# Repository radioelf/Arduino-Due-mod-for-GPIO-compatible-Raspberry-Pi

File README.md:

# Arduino Due mod for GPIO compatible Raspberry Pi
Creative Commons License Disclaimer

UNLESS OTHERWISE MUTUALLY AGREED TO BY THE PARTIES IN WRITING, LICENSOR OFFERS THE WORK AS-IS AND MAKES NO REPRESENTATIONS 
OR WARRANTIES OF ANY KIND CONCERNING THE WORK, EXPRESS, IMPLIED, STATUTORY OR OTHERWISE, INCLUDING, WITHOUT LIMITATION,
WARRANTIES OF TITLE, MERCHANTIBILITY, FITNESS FOR A PARTICULAR PURPOSE, NONINFRINGEMENT, OR THE ABSENCE OF LATENT OR 
OTHER DEFECTS, ACCURACY, OR THE PRESENCE OF ABSENCE OF ERRORS, WHETHER OR NOT DISCOVERABLE. SOME JURISDICTIONS DO NOT 
ALLOW THE EXCLUSION OF IMPLIED WARRANTIES, SO SUCH EXCLUSION MAY NOT APPLY TO YOU. EXCEPT TO THE EXTENT REQUIRED BY 
APPLICABLE LAW, IN NO EVENT WILL LICENSOR BE LIABLE TO YOU ON ANY LEGAL THEORY FOR ANY SPECIAL, INCIDENTAL, CONSEQUENTIAL, 
PUNITIVE OR EXEMPLARY DAMAGES ARISING OUT OF THIS LICENSE OR THE USE OF THE WORK, EVEN IF LICENSOR HAS BEEN ADVISED OF 
THE POSSIBILITY OF SUCH DAMAGES.

http://creativecommons.org/licenses/by-sa/3.0/

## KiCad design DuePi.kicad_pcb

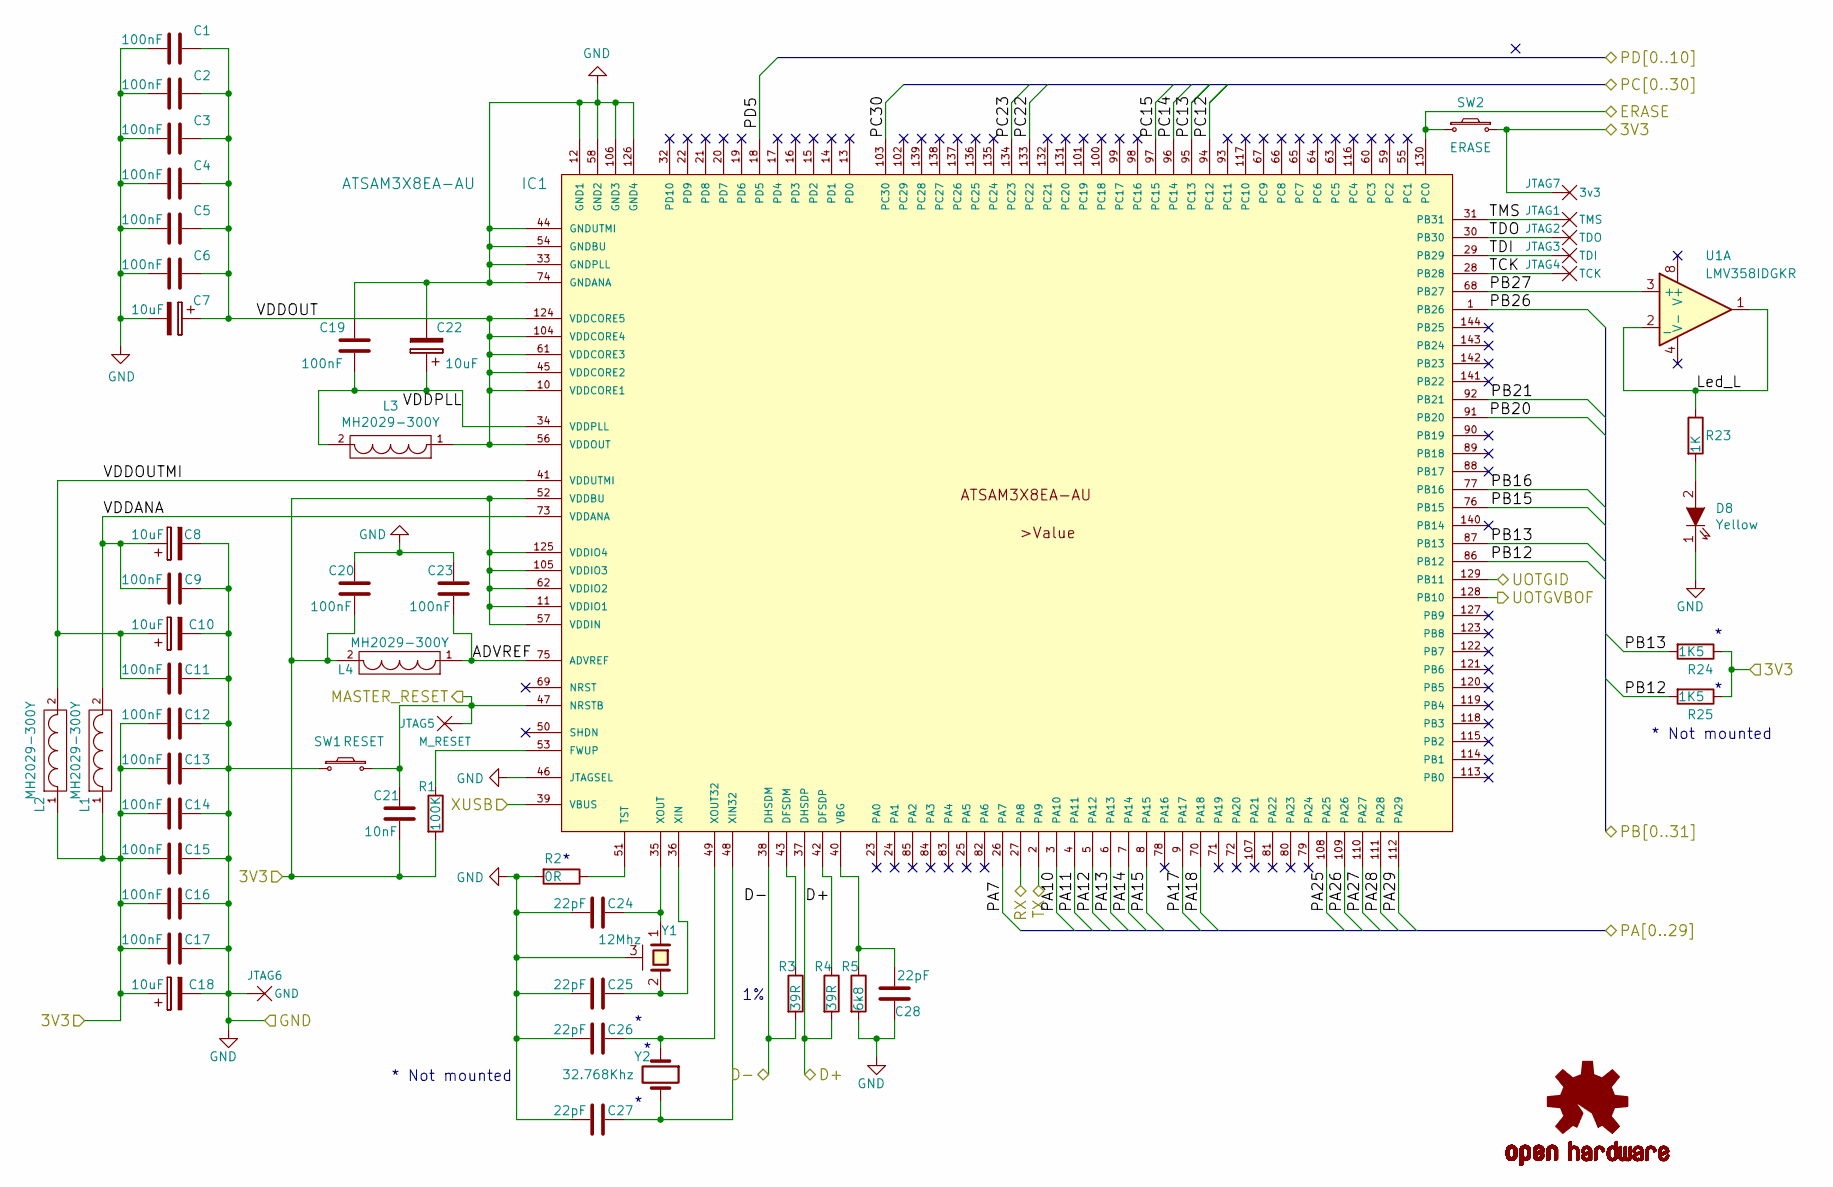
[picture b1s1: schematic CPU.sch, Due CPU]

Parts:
C1, C2, C3, C4, C5, C6, C9, C11, C12, C13, C14, C15, C16, C17, C19, C20, C23: 100nF; C_0402
C7, C8, C10, C18, C22: 10uF; C_1210_HandSoldering
C21: 10nF; C_0402
C24, C25, C26, C27, C28: 22pF; C_0402
D8: Yellow; LED_0603
IC1: ATSAM3X8EA-AU; LQFP-144_20x20mm_Pitch0.5mm
JTAG1: TMS; Measurement_Point_Round-TH_Small
JTAG2: TDO; Measurement_Point_Round-TH_Small
JTAG3: TDI; Measurement_Point_Round-TH_Small
JTAG4: TCK; Measurement_Point_Round-TH_Small
JTAG5: M_RESET; Measurement_Point_Round-TH_Small
JTAG6: GND; Measurement_Point_Round-TH_Small
JTAG7: 3v3; Measurement_Point_Round-TH_Small
L1, L2, L3, L4: MH2029-300Y; R_0805
M2: OSHW-LOGOL; OSHW-LOGO-L
R1: 100K; R_0402
R2: 0R; R_0402
R3, R4: 39R; R_0402
R5: 6k8; R_0603
R23: 1K; R_0402
R24, R25: 1K5; R_0402
SW1: RESET; SW_SPST_B3S-1000
SW2: ERASE; SW_SPST_EVQPE1
U1: LMV358IDGKR; MSOP8
Y1: 12Mhz; Crystal_SMD_2520_4Pads
Y2: 32.768Khz; Crystal_SMD_5032_2Pads

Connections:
/CPU_Due/3V3: C12.1, C13.1, C14.1, C15.1, C16.1, C17.1, C18.1, C20.1, C21.1, IC1.11 (VDDIO1), IC1.52 (VDDBU), IC1.57 (VDDIN), IC1.62 (VDDIO2), IC1.105 (VDDIO3), IC1.125 (VDDIO4), JTAG7.1, L1.1, L2.1, L4.2, R1.2, R24.1, R25.1, SW2.2; also elsewhere on the board
/CPU_Due/ADVREF: C23.1, IC1.75 (ADVREF), L4.1
/CPU_Due/D+: IC1.37 (DHSDP), R4.2; also elsewhere on the board
/CPU_Due/D-: IC1.38 (DHSDM), R3.2; also elsewhere on the board
/CPU_Due/ERASE: IC1.130 (PC0), SW2.1; also elsewhere on the board
/CPU_Due/Led_L: R23.1, U1.1, U1.2 (_)
/CPU_Due/MASTER_RESET: C21.2, IC1.47 (NRSTB), JTAG5.1, SW1.2; also elsewhere on the board
/CPU_Due/PB27: IC1.68 (PB27), U1.3 (+)
/CPU_Due/RX: IC1.27 (PA8); also elsewhere on the board
/CPU_Due/TCK: IC1.28 (PB28), JTAG4.1
/CPU_Due/TDI: IC1.29 (PB29), JTAG3.1
/CPU_Due/TDO: IC1.30 (PB30), JTAG2.1
/CPU_Due/TMS: IC1.31 (PB31), JTAG1.1
/CPU_Due/TX: IC1.2 (PA9); also elsewhere on the board
/CPU_Due/UOTGID: IC1.129 (PB11); also elsewhere on the board
/CPU_Due/UOTGVBOF: IC1.128 (PB10); also elsewhere on the board
/CPU_Due/VDDANA: C8.1, C9.1, IC1.73 (VDDANA), L1.2
/CPU_Due/VDDOUT: C1.2, C2.2, C3.2, C4.2, C5.2, C6.2, C7.1, IC1.10 (VDDCORE1), IC1.45 (VDDCORE2), IC1.56 (VDDOUT), IC1.61 (VDDCORE3), IC1.104 (VDDCORE4), IC1.124 (VDDCORE5), L3.1
/CPU_Due/VDDOUTMI: C10.1, C11.1, IC1.41 (VDDUTMI), L2.2
/CPU_Due/VDDPLL: C19.1, C22.1, IC1.34 (VDDPLL), L3.2
/CPU_Due/XUSB: IC1.39 (VBUS); also elsewhere on the board
/DronPi_GPIO/AUX1: IC1.95 (PC13); also elsewhere on the board
/DronPi_GPIO/AUX2: IC1.94 (PC12); also elsewhere on the board
/DronPi_GPIO/AUX3: IC1.77 (PB16); also elsewhere on the board
/DronPi_GPIO/AUX4: IC1.91 (PB20); also elsewhere on the board
/DronPi_GPIO/AUX5: IC1.96 (PC14); also elsewhere on the board
/DronPi_GPIO/BUZZER: IC1.76 (PB15); also elsewhere on the board
/DronPi_GPIO/CS_BARO: IC1.111 (PA28); also elsewhere on the board
/DronPi_GPIO/CS_CAN: IC1.92 (PB21); also elsewhere on the board
/DronPi_GPIO/CS_MPU: IC1.112 (PA29); also elsewhere on the board
/DronPi_GPIO/CTS: IC1.8 (PA15); also elsewhere on the board
/DronPi_GPIO/ENABLE: IC1.26 (PA7); also elsewhere on the board
/DronPi_GPIO/INT_CAN: IC1.3 (PA10); also elsewhere on the board
/DronPi_GPIO/INT_MPU: IC1.1 (PB26); also elsewhere on the board
/DronPi_GPIO/LED_Green: IC1.134 (PC23); also elsewhere on the board
/DronPi_GPIO/LED_Red: IC1.133 (PC22); also elsewhere on the board
/DronPi_GPIO/LED_Yellow: IC1.103 (PC30); also elsewhere on the board
/DronPi_GPIO/MISO: IC1.108 (PA25); also elsewhere on the board
/DronPi_GPIO/MOSI: IC1.109 (PA26); also elsewhere on the board
/DronPi_GPIO/POWER_OFF: IC1.97 (PC15); also elsewhere on the board
/DronPi_GPIO/PPM: IC1.18 (PD5); also elsewhere on the board
/DronPi_GPIO/PWM_EN: IC1.4 (PA11); also elsewhere on the board
/DronPi_GPIO/RTS: IC1.7 (PA14); also elsewhere on the board
/DronPi_GPIO/RXD: IC1.5 (PA12); also elsewhere on the board
/DronPi_GPIO/SCL: IC1.87 (PB13), R24.2; also elsewhere on the board
/DronPi_GPIO/SCL1: IC1.70 (PA18); also elsewhere on the board
/DronPi_GPIO/SDA: IC1.86 (PB12), R25.2; also elsewhere on the board
/DronPi_GPIO/SDA1: IC1.9 (PA17); also elsewhere on the board
/DronPi_GPIO/SPCK: IC1.110 (PA27); also elsewhere on the board
/DronPi_GPIO/TXD: IC1.6 (PA13); also elsewhere on the board
/Power_Due/+5V: U1.8 (V+); also elsewhere on the board
GND: C1.1, C2.1, C3.1, C4.1, C5.1, C6.1, C7.2, C8.2, C9.2, C10.2, C11.2, C12.2, C13.2, C14.2, C15.2, C16.2, C17.2, C18.2, C19.2, C20.2, C22.2, C23.2, C24.1, C25.1, C26.1, C27.1, C28.2, D8.1 (K), IC1.12 (GND1), IC1.33 (GNDPLL), IC1.44 (GNDUTMI), IC1.46 (JTAGSEL), IC1.54 (GNDBU), IC1.58 (GND2), IC1.74 (GNDANA), IC1.106 (GND3), IC1.126 (GND4), JTAG6.1, R2.2, R5.2, SW1.1, U1.4 (V-), Y1.3 (case); also elsewhere on the board
unnamed: C24.2, IC1.35 (XOUT), Y1.1
unnamed: C25.2, IC1.36 (XIN), Y1.2
unnamed: C26.2, IC1.49 (XOUT32), Y2.1
unnamed: C27.2, IC1.48 (XIN32), Y2.2
unnamed: C28.1, IC1.40 (VBG), R5.1
unnamed: D8.2 (A), R23.2
unnamed: IC1.42 (DFSDP), R4.1
unnamed: IC1.43 (DFSDM), R3.1
unnamed: IC1.51 (TST), R2.1
unnamed: IC1.53 (FWUP), R1.1

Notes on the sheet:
* Not mounted

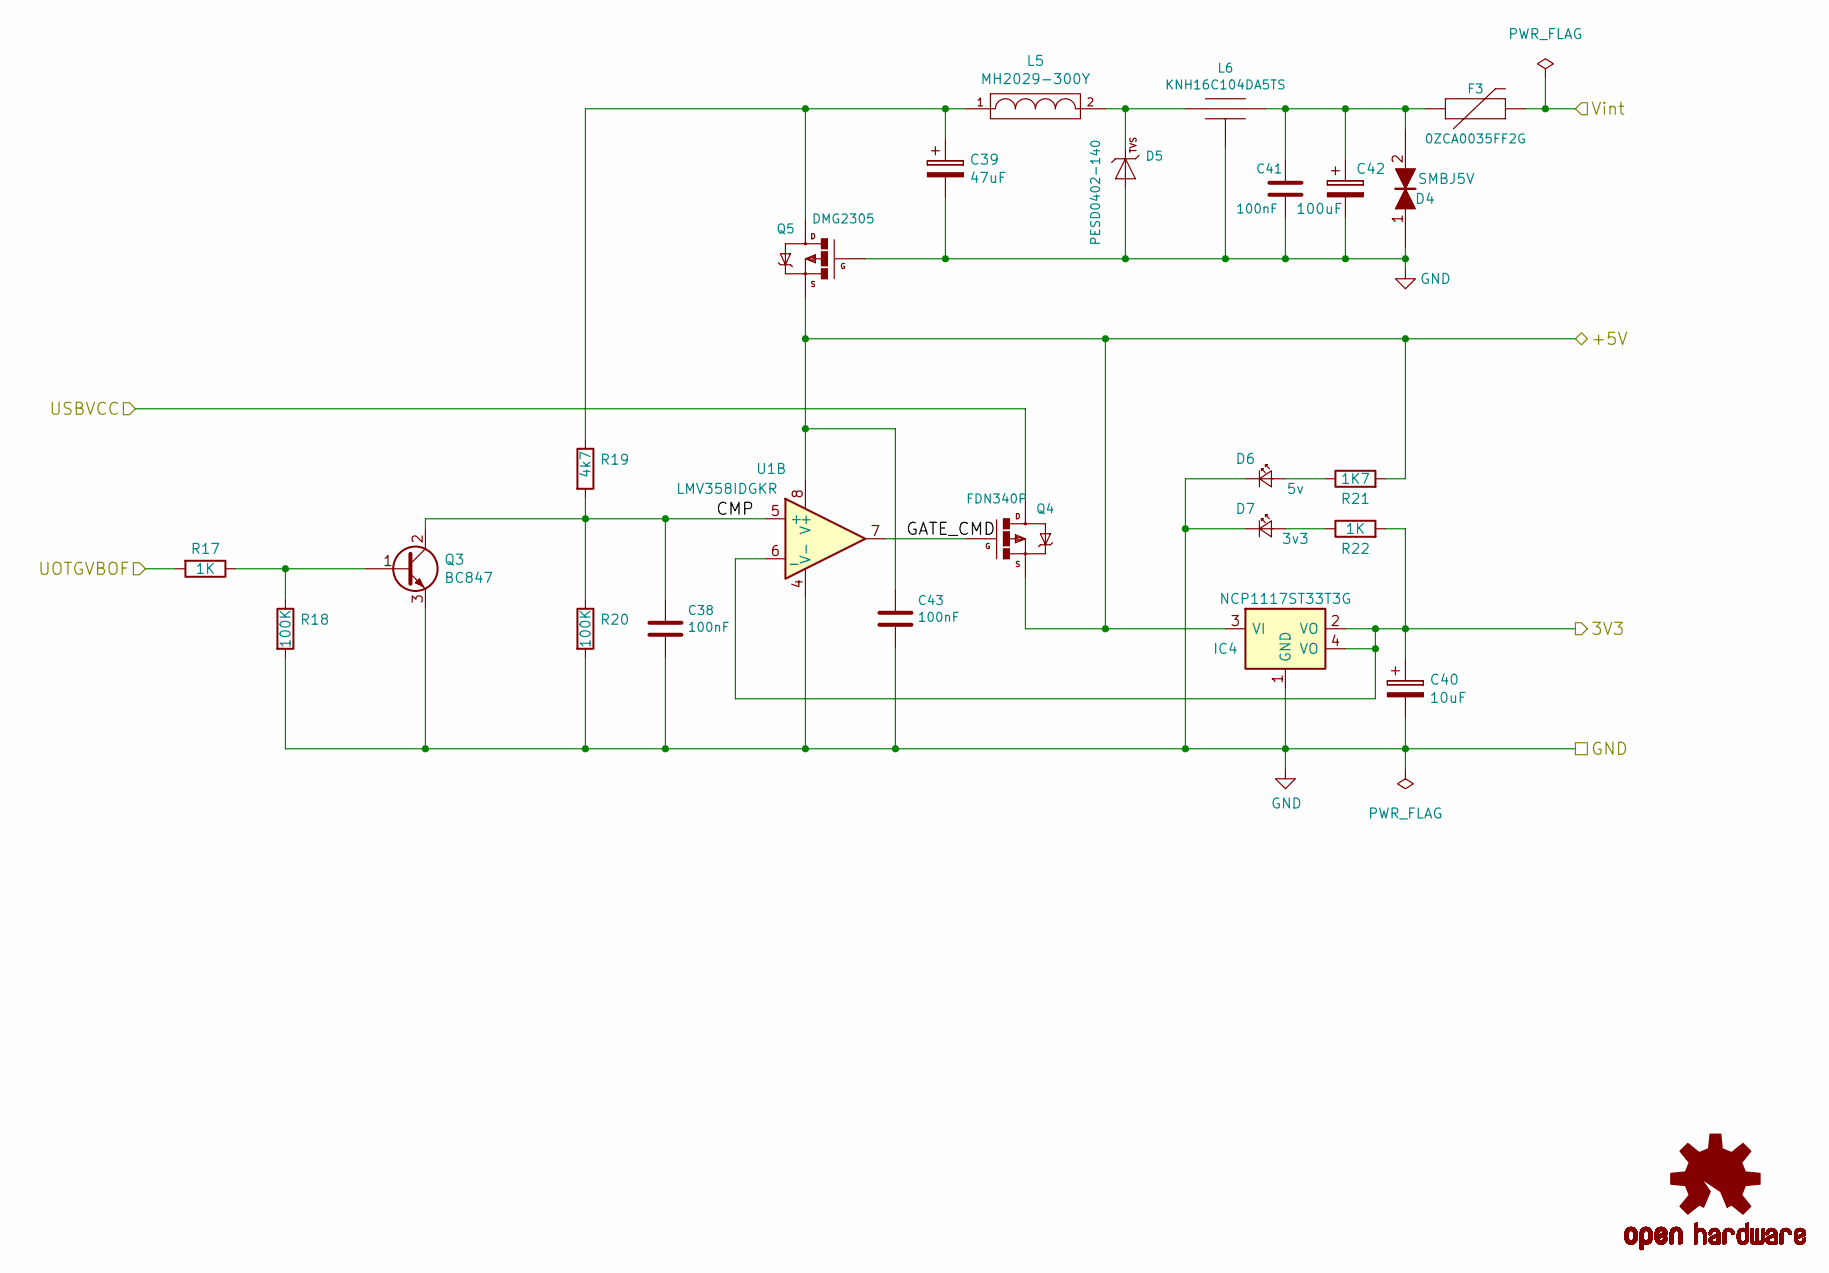
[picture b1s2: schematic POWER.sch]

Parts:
C38, C41, C43: 100nF; C_0402
C39: 47uF; C_1210_HandSoldering
C40: 10uF; C_1210_HandSoldering
C42: 100uF; TantalC_SizeD_EIA-7343_Reflow
D4: SMBJ5V; DO-214AA
D5: PESD0402-140; C_0402
D6: 5v; LED_0603
D7: 3v3; LED_0603
F3: 0ZCA0035FF2G; Fuse_SMD1206_Wave
IC4: NCP1117ST33T3G; SOT-223
L5: MH2029-300Y; R_0805
L6: KNH16C104DA5TS; KYOCERA-KNH16-DA
M3: OSHW-LOGOL; OSHW-LOGO-L
Q3: BC847; SOT-23
Q4: FDN340P; SOT-23
Q5: DMG2305; SOT-23
R17, R22: 1K; R_0402
R18, R20: 100K; R_0402
R19: 4k7; R_0402
R21: 1K7; R_0402
U1: LMV358IDGKR; MSOP8

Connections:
/CPU_Due/3V3: C40.1, IC4.2 (VO), IC4.4 (VO), R22.2, U1.6 (_); also elsewhere on the board
/CPU_Due/UOTGVBOF: R17.2; also elsewhere on the board
/DronPi_GPIO/Vint: F3.2; also elsewhere on the board
/Power_Due/+5V: C43.1, IC4.3 (VI), Q4.2 (S), Q5.2 (S), R21.2, U1.8 (V+); also elsewhere on the board
/Power_Due/CMP: C38.1, Q3.2 (C), R19.2, R20.1, U1.5 (+)
/Power_Due/GATE_CMD: Q4.1 (G), U1.7
/Power_Due/USBVCC: Q4.3 (D); also elsewhere on the board
GND: C38.2, C39.2, C40.2, C41.2, C42.2, C43.2, D4.1, D5.2 (A), D6.1 (K), D7.1 (K), IC4.1 (GND), L6.P$3, L6.P$4, L6.P$5, Q3.3 (E), Q5.1 (G), R18.2, R20.2, U1.4 (V-); also elsewhere on the board
unnamed: C39.1, L5.1, Q5.3 (D), R19.1
unnamed: C41.1, C42.1, D4.2, F3.1, L6.P$2
unnamed: D5.1 (C), L5.2, L6.P$1
unnamed: D6.2 (A), R21.1
unnamed: D7.2 (A), R22.1
unnamed: Q3.1 (B), R17.1, R18.1

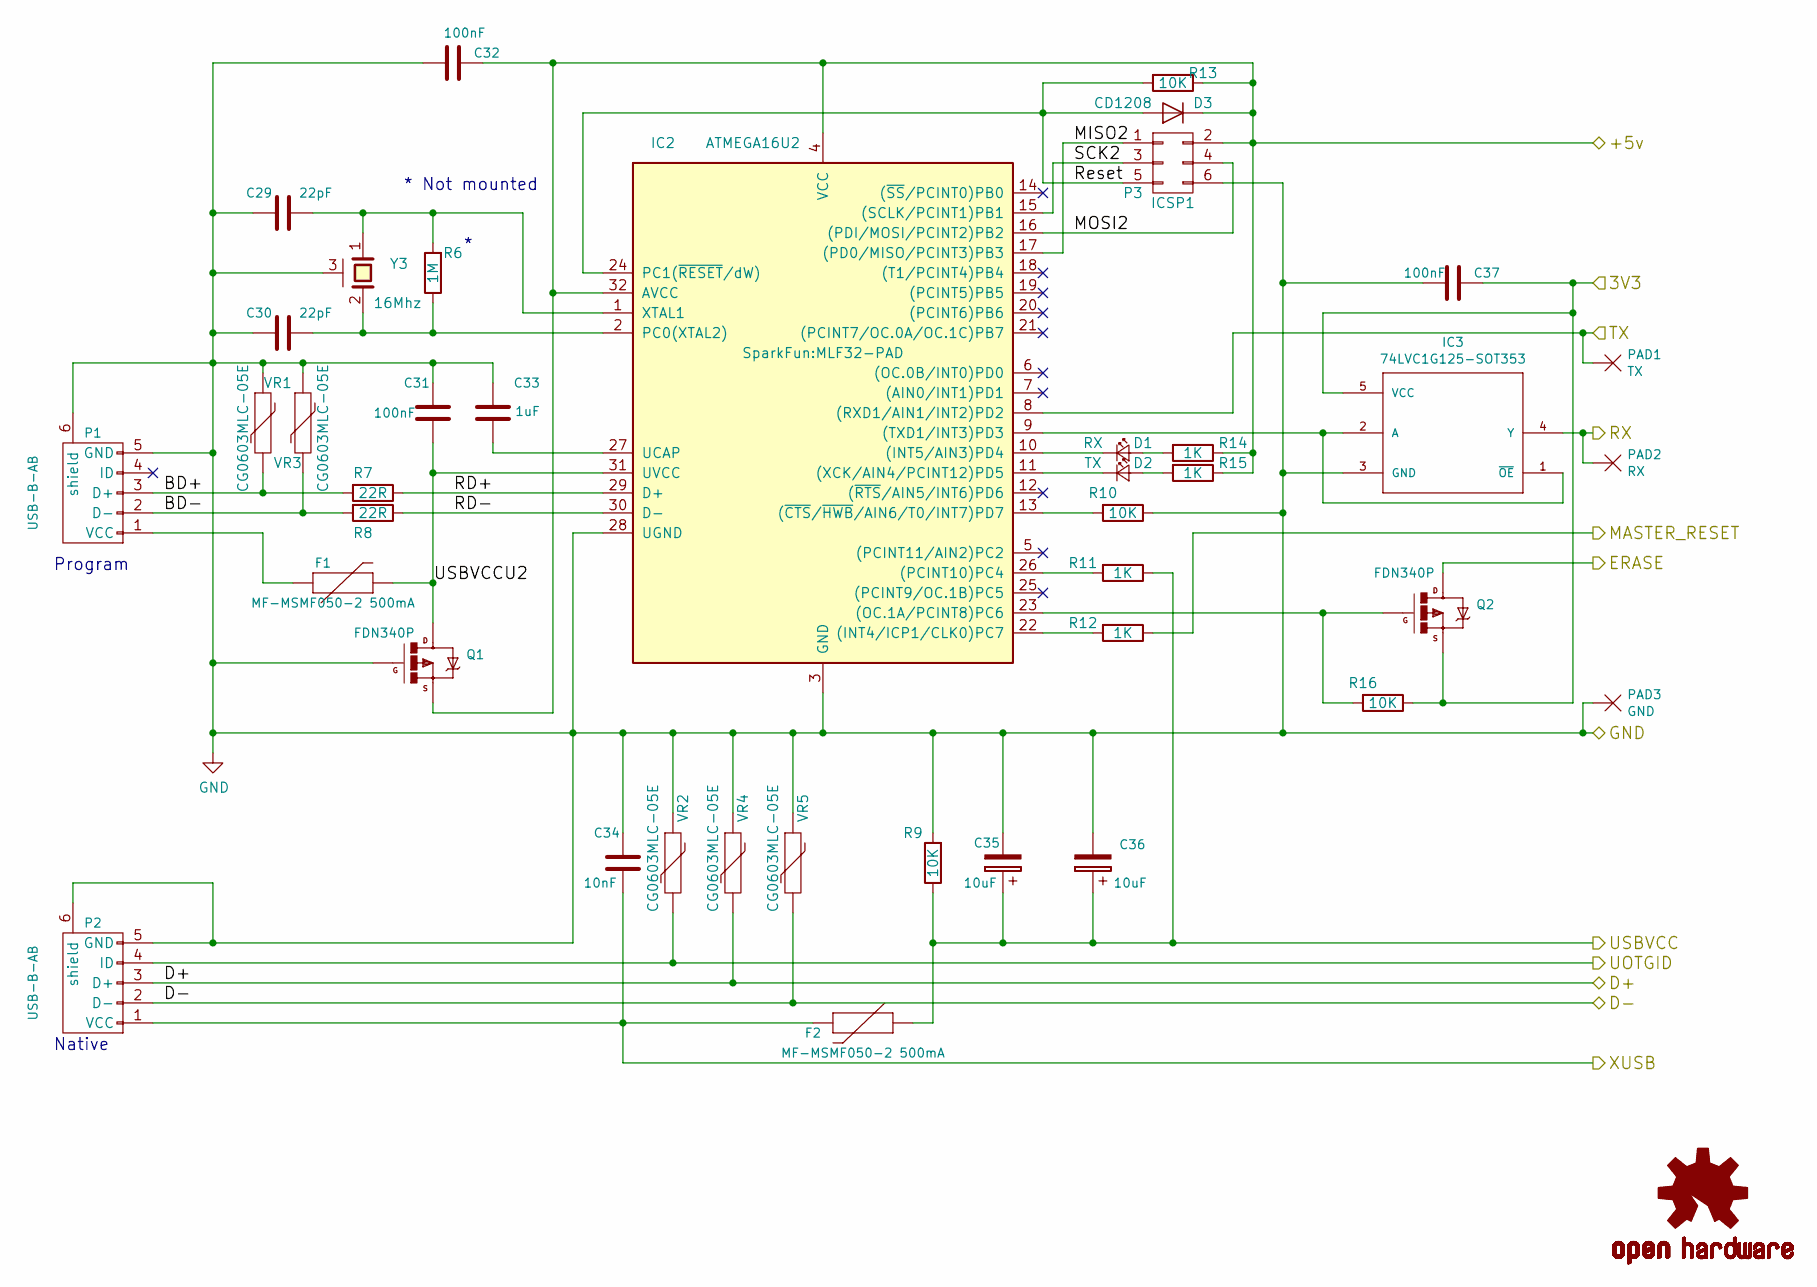
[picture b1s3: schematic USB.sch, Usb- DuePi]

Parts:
C29, C30: 22pF; C_0402
C31, C32, C37: 100nF; C_0402
C33: 1uF; C_0402
C34: 10nF; C_0402
C35, C36: 10uF; C_1210_HandSoldering
D1: RX; LED_0603
D2: TX; LED_0603
D3: CD1208; D_1206
F1, F2: MF-MSMF050-2 500mA; Neosid_Inductor_SM-NE45_SMD1812
IC2: ATMEGA16U2; MLF32-PAD
IC3: 74LVC1G125-SOT353; SC70-5
M5: OSHW-LOGOL; OSHW-LOGO-L
P1, P2: USB-B-AB; USB_Micro-B
P3: ICSP1; Pin_Header_Straight_2x03
PAD1: TX; Measurement_Point_Square-TH_Small
PAD2: RX; Measurement_Point_Square-TH_Small
PAD3: GND; Measurement_Point_Square-TH_Small
Q1, Q2: FDN340P; SOT-23
R6: 1M; R_0402
R7, R8: 22R; R_0402
R9, R10, R13, R16: 10K; R_0402
R11, R12, R14, R15: 1K; R_0402
VR1, VR2, VR3, VR4, VR5: CG0603MLC-05E; Neosid_Inductor_SM0603CG
Y3: 16Mhz; Crystal_SMD_2520_4Pads

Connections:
/CPU_Due/3V3: C37.1, IC3.5 (VCC), Q2.2 (S), R16.1; also elsewhere on the board
/CPU_Due/D+: P2.3 (D+), VR4.2; also elsewhere on the board
/CPU_Due/D-: P2.2 (D-), VR5.2; also elsewhere on the board
/CPU_Due/ERASE: Q2.3 (D); also elsewhere on the board
/CPU_Due/MASTER_RESET: R12.1; also elsewhere on the board
/CPU_Due/RX: IC3.4 (Y), PAD2.1; also elsewhere on the board
/CPU_Due/TX: IC2.8 ((RXD1/AIN1/INT2)PD2), PAD1.1; also elsewhere on the board
/CPU_Due/UOTGID: P2.4 (ID), VR2.2; also elsewhere on the board
/CPU_Due/XUSB: C34.2, F2.2, P2.1 (VCC); also elsewhere on the board
/Power_Due/+5V: C32.1, D3.1 (K), IC2.4 (VCC), IC2.32 (AVCC), P3.2, Q1.2 (S), R13.1, R14.1, R15.1; also elsewhere on the board
/Power_Due/USBVCC: C35.1, C36.1, F2.1, R9.1, R11.1; also elsewhere on the board
/USB_Due/BD+: P1.3 (D+), R7.2, VR1.2
/USB_Due/BD-: P1.2 (D-), R8.2, VR3.2
/USB_Due/MISO2: IC2.17 ((PD0/MISO/PCINT3)PB3), P3.1
/USB_Due/MOSI2: IC2.16 ((PDI/MOSI/PCINT2)PB2), P3.4
/USB_Due/RD+: IC2.29 (D+), R7.1
/USB_Due/RD-: IC2.30 (D-), R8.1
/USB_Due/Reset: D3.2 (A), IC2.24 (PC1(~RESET~/dW)), P3.5, R13.2
/USB_Due/SCK2: IC2.15 ((SCLK/PCINT1)PB1), P3.3
/USB_Due/USBVCCU2: C31.2, F1.2, IC2.31 (UVCC), Q1.3 (D)
GND: C29.1, C30.1, C31.1, C32.2, C33.1, C34.1, C35.2, C36.2, C37.2, IC2.3 (GND), IC2.28 (UGND), IC3.3 (GND), P1.5 (GND), P1.6 (shield), P2.5 (GND), P2.6 (shield), P3.6, PAD3.1, Q1.1 (G), R9.2, R10.1, VR1.1, VR2.1, VR3.1, VR4.1, VR5.1, Y3.3 (case); also elsewhere on the board
unnamed: C29.2, IC2.1 (XTAL1), R6.2, Y3.1
unnamed: C30.2, IC2.2 (PC0(XTAL2)), R6.1, Y3.2
unnamed: C33.2, IC2.27 (UCAP)
unnamed: D1.1 (K), IC2.10 ((INT5/AIN3)PD4)
unnamed: D1.2 (A), R14.2
unnamed: D2.1 (K), IC2.11 ((XCK/AIN4/PCINT12)PD5)
unnamed: D2.2 (A), R15.2
unnamed: F1.1, P1.1 (VCC)
unnamed: IC2.9 ((TXD1/INT3)PD3), IC3.1 (~OE), IC3.2 (A)
unnamed: IC2.13 ((~CTS~/~HWB~/AIN6/T0/INT7)PD7), R10.2
unnamed: IC2.22 ((INT4/ICP1/CLK0)PC7), R12.2
unnamed: IC2.23 ((OC.1A/PCINT8)PC6), Q2.1 (G), R16.2
unnamed: IC2.26 ((PCINT10)PC4), R11.2

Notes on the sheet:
Program
Native
* Not mounted

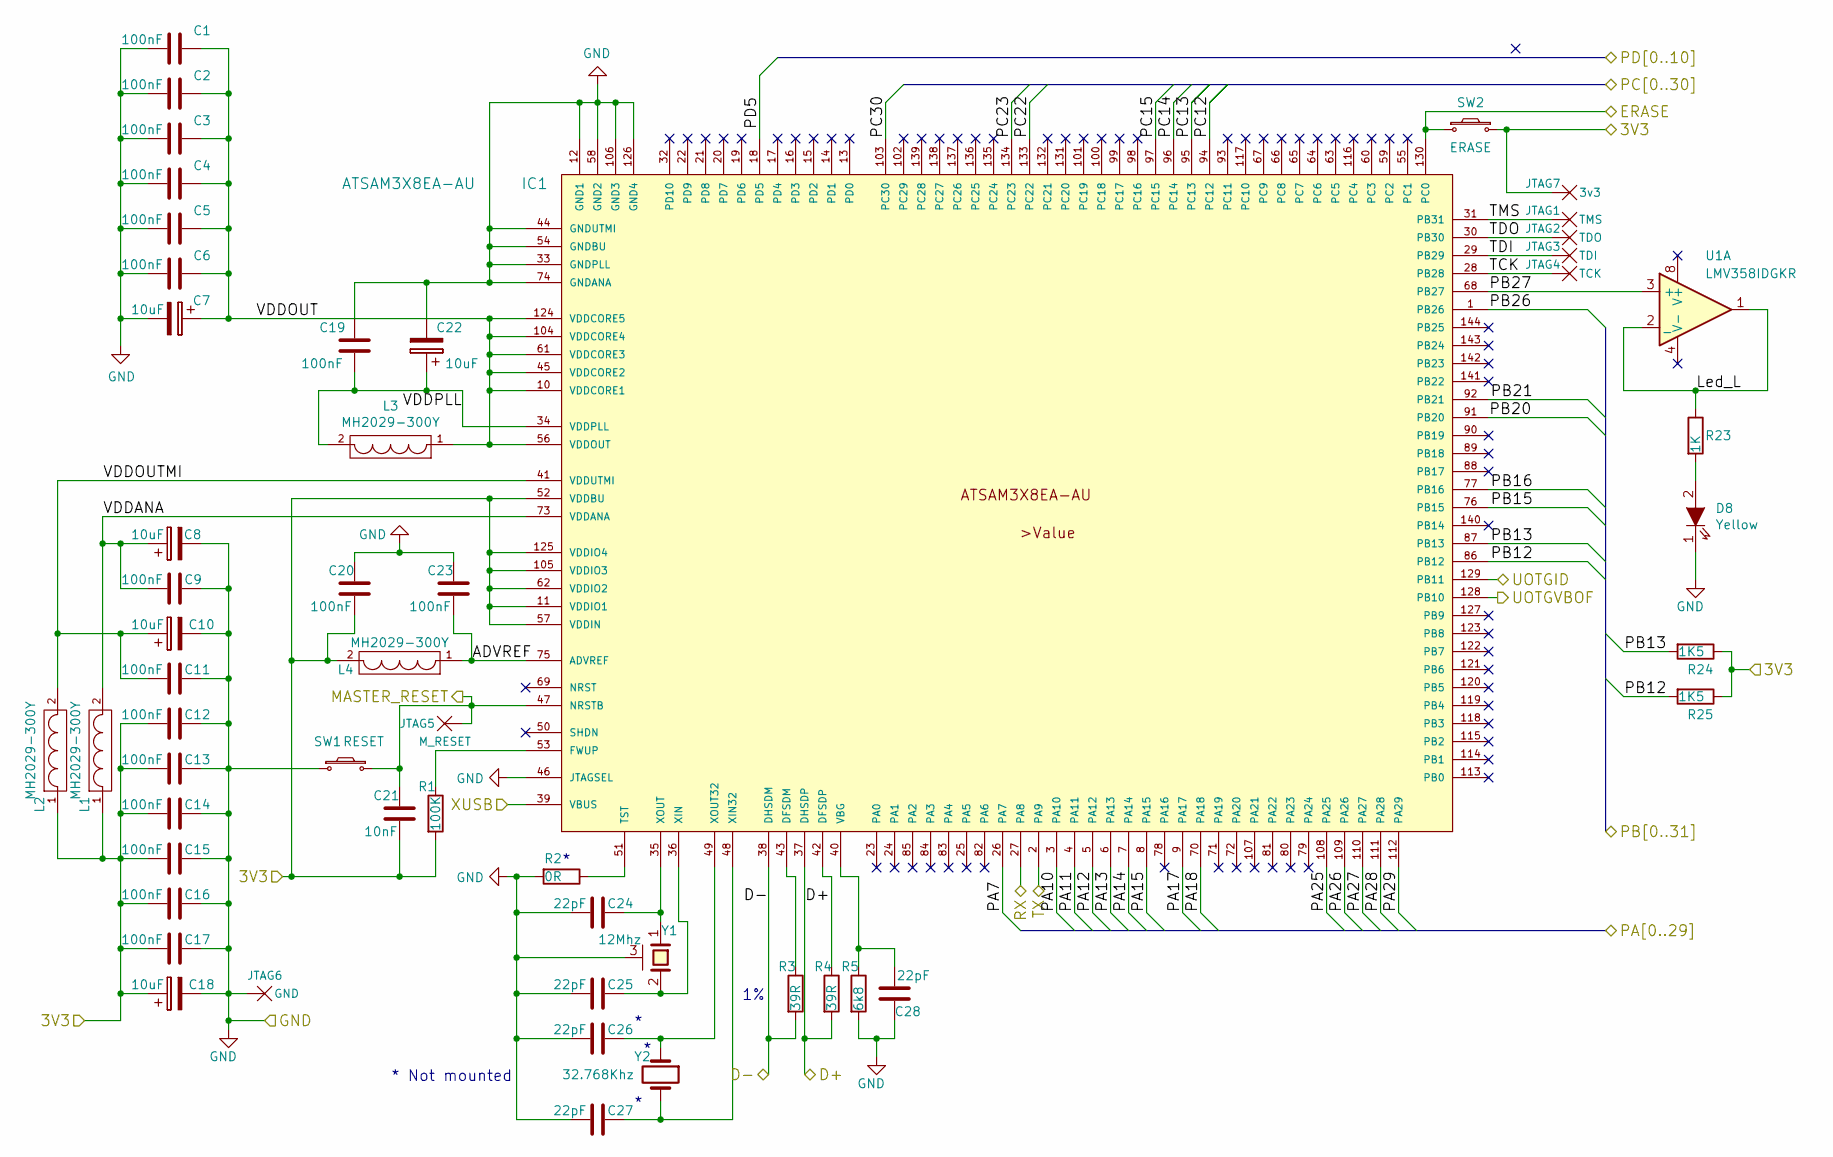
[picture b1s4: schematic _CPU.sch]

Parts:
C1, C2, C3, C4, C5, C6, C9, C11, C12, C13, C14, C15, C16, C17, C19, C20, C23: 100nF; C_0402
C7, C8, C10, C18, C22: 10uF; C_1210_HandSoldering
C21: 10nF; C_0402
C24, C25, C26, C27, C28: 22pF; C_0402
D8: Yellow; LED_0603
IC1: ATSAM3X8EA-AU; LQFP-144_20x20mm_Pitch0.5mm
JTAG1: TMS; Measurement_Point_Round-TH_Small
JTAG2: TDO; Measurement_Point_Round-TH_Small
JTAG3: TDI; Measurement_Point_Round-TH_Small
JTAG4: TCK; Measurement_Point_Round-TH_Small
JTAG5: M_RESET; Measurement_Point_Round-TH_Small
JTAG6: GND; Measurement_Point_Round-TH_Small
JTAG7: 3v3; Measurement_Point_Round-TH_Small
L1, L2, L3, L4: MH2029-300Y; R_0805
R1: 100K; R_0402
R2: 0R; R_0402
R3, R4: 39R; R_0402
R5: 6k8; R_0603
R23: 1K; R_0402
R24, R25: 1K5; R_0402
SW1: RESET; SW_SPST_B3S-1000
SW2: ERASE; SW_SPST_EVQPE1
U1: LMV358IDGKR; MSOP8
Y1: 12Mhz; Crystal_SMD_2520_4Pads
Y2: 32.768Khz; Crystal_SMD_5032_2Pads

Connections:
/CPU_Due/3V3: C12.1, C13.1, C14.1, C15.1, C16.1, C17.1, C18.1, C20.1, C21.1, IC1.11 (VDDIO1), IC1.52 (VDDBU), IC1.57 (VDDIN), IC1.62 (VDDIO2), IC1.105 (VDDIO3), IC1.125 (VDDIO4), JTAG7.1, L1.1, L2.1, L4.2, R1.2, R24.1, R25.1, SW2.2; also elsewhere on the board
/CPU_Due/ADVREF: C23.1, IC1.75 (ADVREF), L4.1
/CPU_Due/D+: IC1.37 (DHSDP), R4.2; also elsewhere on the board
/CPU_Due/D-: IC1.38 (DHSDM), R3.2; also elsewhere on the board
/CPU_Due/ERASE: IC1.130 (PC0), SW2.1; also elsewhere on the board
/CPU_Due/Led_L: R23.1, U1.1, U1.2 (_)
/CPU_Due/MASTER_RESET: C21.2, IC1.47 (NRSTB), JTAG5.1, SW1.2; also elsewhere on the board
/CPU_Due/PB27: IC1.68 (PB27), U1.3 (+)
/CPU_Due/RX: IC1.27 (PA8); also elsewhere on the board
/CPU_Due/TCK: IC1.28 (PB28), JTAG4.1
/CPU_Due/TDI: IC1.29 (PB29), JTAG3.1
/CPU_Due/TDO: IC1.30 (PB30), JTAG2.1
/CPU_Due/TMS: IC1.31 (PB31), JTAG1.1
/CPU_Due/TX: IC1.2 (PA9); also elsewhere on the board
/CPU_Due/UOTGID: IC1.129 (PB11); also elsewhere on the board
/CPU_Due/UOTGVBOF: IC1.128 (PB10); also elsewhere on the board
/CPU_Due/VDDANA: C8.1, C9.1, IC1.73 (VDDANA), L1.2
/CPU_Due/VDDOUT: C1.2, C2.2, C3.2, C4.2, C5.2, C6.2, C7.1, IC1.10 (VDDCORE1), IC1.45 (VDDCORE2), IC1.56 (VDDOUT), IC1.61 (VDDCORE3), IC1.104 (VDDCORE4), IC1.124 (VDDCORE5), L3.1
/CPU_Due/VDDOUTMI: C10.1, C11.1, IC1.41 (VDDUTMI), L2.2
/CPU_Due/VDDPLL: C19.1, C22.1, IC1.34 (VDDPLL), L3.2
/CPU_Due/XUSB: IC1.39 (VBUS); also elsewhere on the board
/DronPi_GPIO/AUX1: IC1.95 (PC13); also elsewhere on the board
/DronPi_GPIO/AUX2: IC1.94 (PC12); also elsewhere on the board
/DronPi_GPIO/AUX3: IC1.77 (PB16); also elsewhere on the board
/DronPi_GPIO/AUX4: IC1.91 (PB20); also elsewhere on the board
/DronPi_GPIO/AUX5: IC1.96 (PC14); also elsewhere on the board
/DronPi_GPIO/BUZZER: IC1.76 (PB15); also elsewhere on the board
/DronPi_GPIO/CS_BARO: IC1.111 (PA28); also elsewhere on the board
/DronPi_GPIO/CS_CAN: IC1.92 (PB21); also elsewhere on the board
/DronPi_GPIO/CS_MPU: IC1.112 (PA29); also elsewhere on the board
/DronPi_GPIO/CTS: IC1.8 (PA15); also elsewhere on the board
/DronPi_GPIO/ENABLE: IC1.26 (PA7); also elsewhere on the board
/DronPi_GPIO/INT_CAN: IC1.3 (PA10); also elsewhere on the board
/DronPi_GPIO/INT_MPU: IC1.1 (PB26); also elsewhere on the board
/DronPi_GPIO/LED_Green: IC1.134 (PC23); also elsewhere on the board
/DronPi_GPIO/LED_Red: IC1.133 (PC22); also elsewhere on the board
/DronPi_GPIO/LED_Yellow: IC1.103 (PC30); also elsewhere on the board
/DronPi_GPIO/MISO: IC1.108 (PA25); also elsewhere on the board
/DronPi_GPIO/MOSI: IC1.109 (PA26); also elsewhere on the board
/DronPi_GPIO/POWER_OFF: IC1.97 (PC15); also elsewhere on the board
/DronPi_GPIO/PPM: IC1.18 (PD5); also elsewhere on the board
/DronPi_GPIO/PWM_EN: IC1.4 (PA11); also elsewhere on the board
/DronPi_GPIO/RTS: IC1.7 (PA14); also elsewhere on the board
/DronPi_GPIO/RXD: IC1.5 (PA12); also elsewhere on the board
/DronPi_GPIO/SCL: IC1.87 (PB13), R24.2; also elsewhere on the board
/DronPi_GPIO/SCL1: IC1.70 (PA18); also elsewhere on the board
/DronPi_GPIO/SDA: IC1.86 (PB12), R25.2; also elsewhere on the board
/DronPi_GPIO/SDA1: IC1.9 (PA17); also elsewhere on the board
/DronPi_GPIO/SPCK: IC1.110 (PA27); also elsewhere on the board
/DronPi_GPIO/TXD: IC1.6 (PA13); also elsewhere on the board
/Power_Due/+5V: U1.8 (V+); also elsewhere on the board
GND: C1.1, C2.1, C3.1, C4.1, C5.1, C6.1, C7.2, C8.2, C9.2, C10.2, C11.2, C12.2, C13.2, C14.2, C15.2, C16.2, C17.2, C18.2, C19.2, C20.2, C22.2, C23.2, C24.1, C25.1, C26.1, C27.1, C28.2, D8.1 (K), IC1.12 (GND1), IC1.33 (GNDPLL), IC1.44 (GNDUTMI), IC1.46 (JTAGSEL), IC1.54 (GNDBU), IC1.58 (GND2), IC1.74 (GNDANA), IC1.106 (GND3), IC1.126 (GND4), JTAG6.1, R2.2, R5.2, SW1.1, U1.4 (V-), Y1.3 (case); also elsewhere on the board
unnamed: C24.2, IC1.35 (XOUT), Y1.1
unnamed: C25.2, IC1.36 (XIN), Y1.2
unnamed: C26.2, IC1.49 (XOUT32), Y2.1
unnamed: C27.2, IC1.48 (XIN32), Y2.2
unnamed: C28.1, IC1.40 (VBG), R5.1
unnamed: D8.2 (A), R23.2
unnamed: IC1.42 (DFSDP), R4.1
unnamed: IC1.43 (DFSDM), R3.1
unnamed: IC1.51 (TST), R2.1
unnamed: IC1.53 (FWUP), R1.1

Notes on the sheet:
* Not mounted

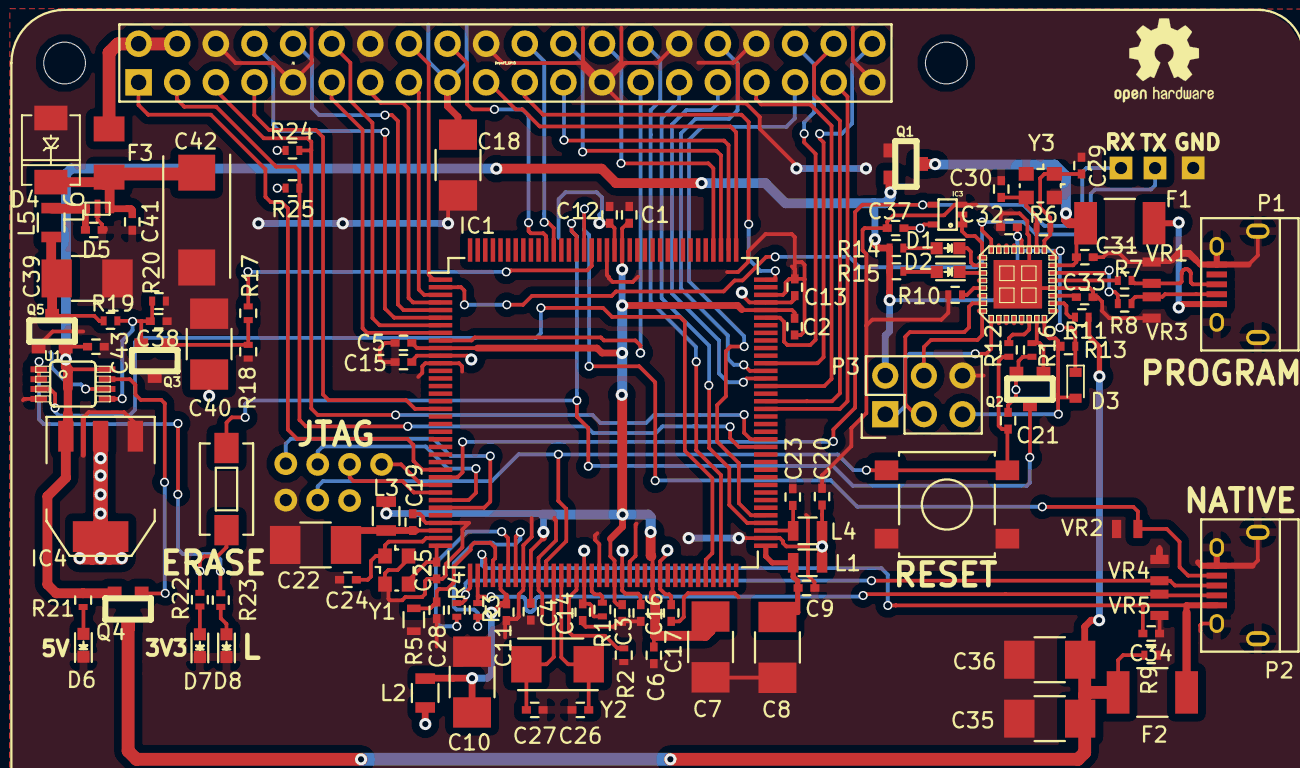
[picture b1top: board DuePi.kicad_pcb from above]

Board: 2 copper layers, 120 parts (0 on the bottom side), 94 nets.

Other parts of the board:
J1: DronPi_GPIO; raspberrypi2
M1: OSHW-LOGOL; OSHW-Logo2_7.3x6mm_SilkScreen

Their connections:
/CPU_Due/3V3: J1.17; also elsewhere on the board
/DronPi_GPIO/AUX1: J1.31; also elsewhere on the board
/DronPi_GPIO/AUX2: J1.33; also elsewhere on the board
/DronPi_GPIO/AUX3: J1.35; also elsewhere on the board
/DronPi_GPIO/AUX4: J1.37; also elsewhere on the board
/DronPi_GPIO/AUX5: J1.32; also elsewhere on the board
/DronPi_GPIO/BUZZER: J1.29; also elsewhere on the board
/DronPi_GPIO/CS_BARO: J1.24; also elsewhere on the board
/DronPi_GPIO/CS_CAN: J1.38; also elsewhere on the board
/DronPi_GPIO/CS_MPU: J1.26; also elsewhere on the board
/DronPi_GPIO/CTS: J1.11; also elsewhere on the board
/DronPi_GPIO/ENABLE: J1.1; also elsewhere on the board
/DronPi_GPIO/INT_CAN: J1.15; also elsewhere on the board
/DronPi_GPIO/INT_MPU: J1.16; also elsewhere on the board
/DronPi_GPIO/LED_Green: J1.18; also elsewhere on the board
/DronPi_GPIO/LED_Red: J1.22; also elsewhere on the board
/DronPi_GPIO/LED_Yellow: J1.36; also elsewhere on the board
/DronPi_GPIO/MISO: J1.21; also elsewhere on the board
/DronPi_GPIO/MOSI: J1.19; also elsewhere on the board
/DronPi_GPIO/POWER_OFF: J1.40; also elsewhere on the board
/DronPi_GPIO/PPM: J1.7; also elsewhere on the board
/DronPi_GPIO/PWM_EN: J1.13; also elsewhere on the board
/DronPi_GPIO/RTS: J1.12; also elsewhere on the board
/DronPi_GPIO/RXD: J1.10; also elsewhere on the board
/DronPi_GPIO/SCL: J1.5; also elsewhere on the board
/DronPi_GPIO/SCL1: J1.28; also elsewhere on the board
/DronPi_GPIO/SDA: J1.3; also elsewhere on the board
/DronPi_GPIO/SDA1: J1.27; also elsewhere on the board
/DronPi_GPIO/SPCK: J1.23; also elsewhere on the board
/DronPi_GPIO/TXD: J1.8; also elsewhere on the board
/DronPi_GPIO/Vint: J1.2, J1.4; also elsewhere on the board
GND: J1.6, J1.9, J1.14, J1.20, J1.25, J1.30, J1.34, J1.39; also elsewhere on the board

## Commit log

2017-02-08 Create Gerber
2017-02-08 Files Gerber for DuePi
2017-02-09 Mapping Pin Arduino Due- DuePi
2017-02-13 Library DuePi
2017-04-18 PCB Image V1.0.1
